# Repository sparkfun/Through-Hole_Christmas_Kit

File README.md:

**NOTE:** *This product has been retired from our catalog.*

Through-Hole Christmas Kit
==========================

[  
*It's A Through-Hole Christmas, Charlie Brown! (KIT-09565)*](https://www.sparkfun.com/products/9565)

This ornamental kit comes with a neatly-cut, tree-shaped PCB, adorned with super-bright green LEDs, and topped with a yellow LED.
The LEDs are controlled by a pre-programmed ATtiny85 AVR, and the circuit is powered by a couple AA batteries. 
All compnents are through-hole, so this is a great kit for that first-time solderer. 

Repository Contents
-------------------
* **/Firmware** - Firmware that ships on the ATtiny85
* **/Hardware** - All Eagle design files (.brd, .sch)

License Information
-------------------
The hardware is released under [Creative Commons Share-alike 3.0](http://creativecommons.org/licenses/by-sa/3.0/).  
All other code is open source so please feel free to do anything you want with it; you buy me a beer if you use this and we meet someday ([Beerware license](http://en.wikipedia.org/wiki/Beerware)).

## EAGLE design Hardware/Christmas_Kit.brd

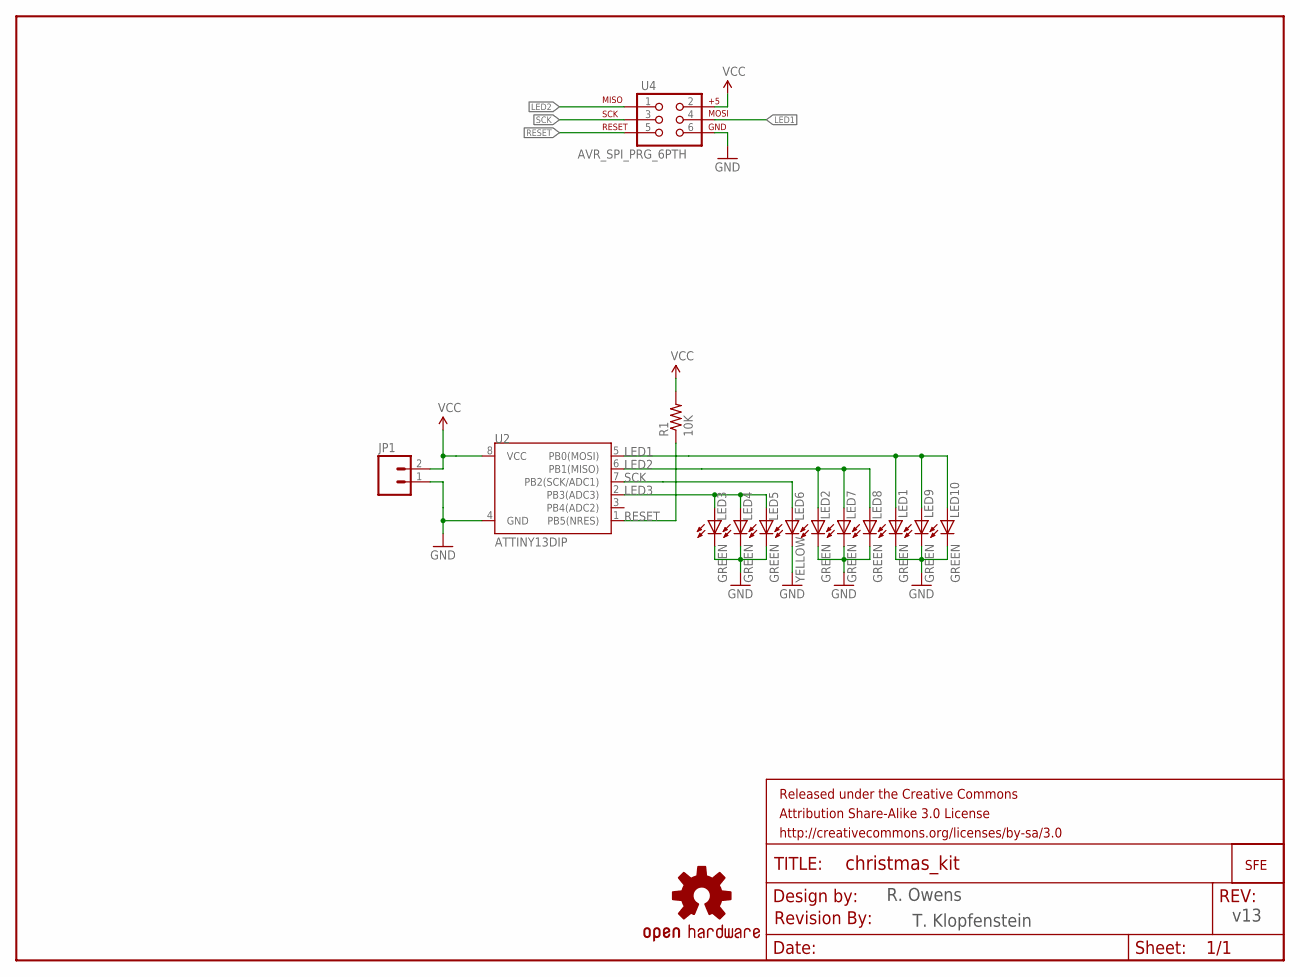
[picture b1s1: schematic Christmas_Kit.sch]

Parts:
FRAME1: FRAME-LETTER; CREATIVE_COMMONS
JP1: M02PTH; 1X02
JP2: LOGO-SFENEW; SFE-NEW-WEBLOGO
LED1, LED2, LED3, LED4, LED5, LED7, LED8, LED9, LED10: GREEN; LED5MM
LED6: YELLOW; LED3MM
LOGO1: OSHW-LOGOL; OSHW-LOGO-L
R1: 10K; AXIAL-0.3
U2: ATTINY13DIP; DIP08
U4: AVR_SPI_PRG_6PTH; 2X3
U$1: REVISION

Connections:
GND: JP1.1, LED1.K (C), LED2.K (C), LED3.K (C), LED4.K (C), LED5.K (C), LED6.K (C), LED7.K (C), LED8.K (C), LED9.K (C), LED10.K (C), U2.4 (GND), U4.6
LED1: LED1.A, LED9.A, LED10.A, U2.5 (PB0(MOSI)), U4.4
LED2: LED2.A, LED7.A, LED8.A, U2.6 (PB1(MISO)), U4.1
LED3: LED3.A, LED4.A, LED5.A, U2.2 (PB3(ADC3))
RESET: R1.P$1 (1), U2.1 (PB5(NRES)), U4.5
SCK: LED6.A, U2.7 (PB2(SCK/ADC1)), U4.3
VCC: JP1.2, R1.P$2 (2), U2.8 (VCC), U4.2

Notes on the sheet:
R. Owens
v13
T. Klopfenstein

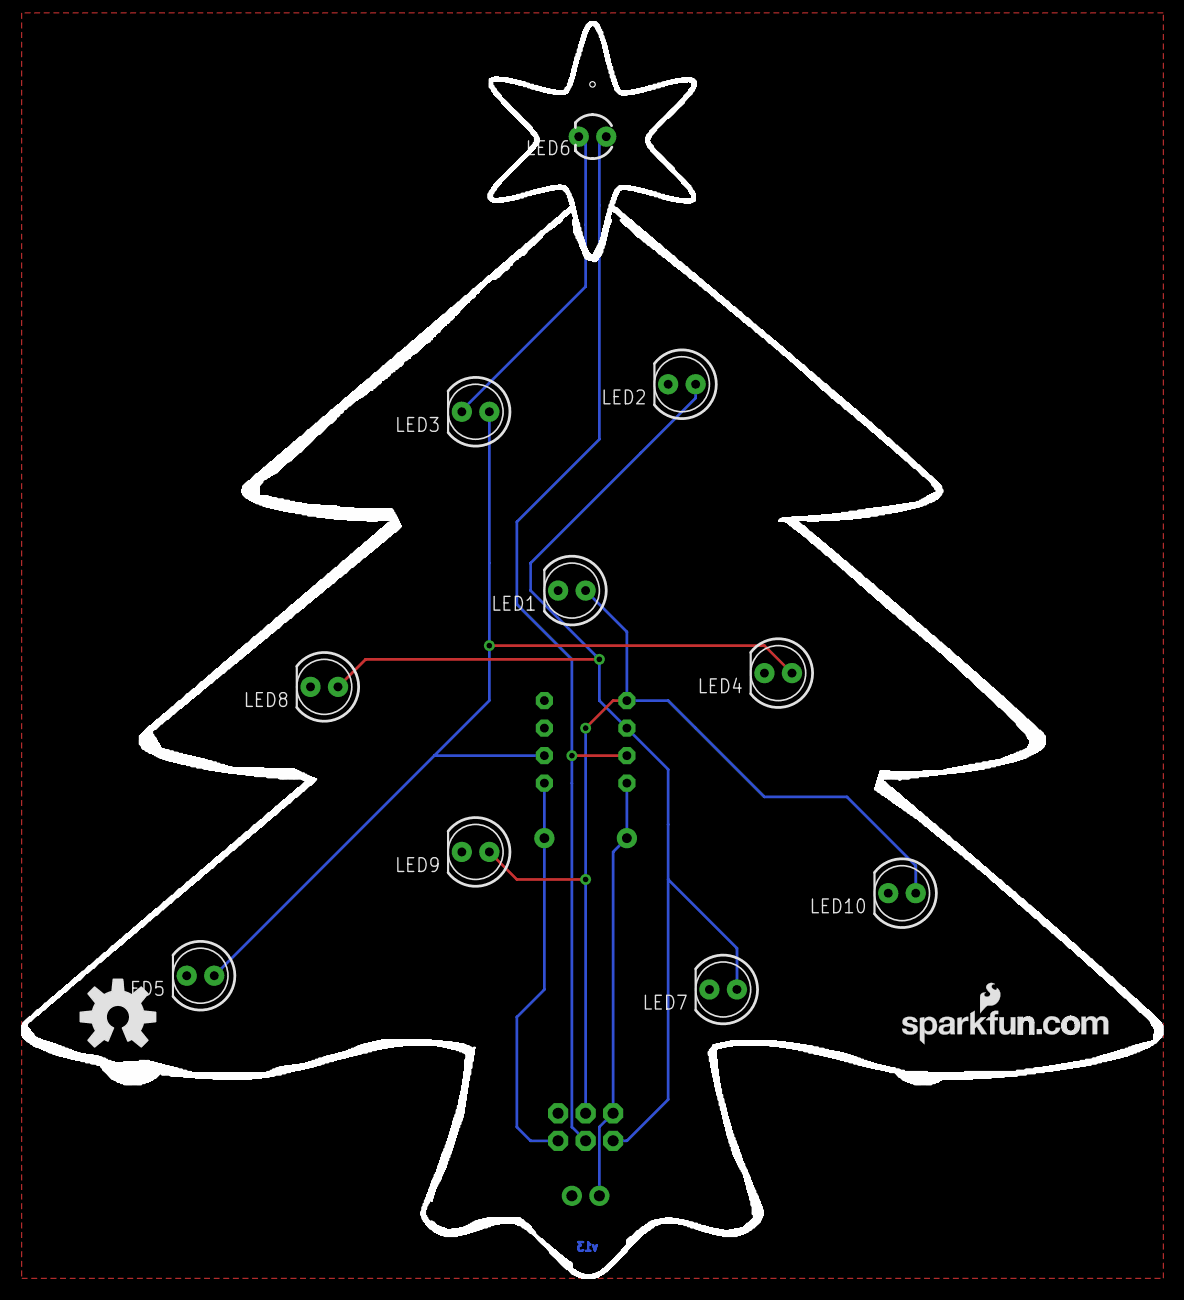
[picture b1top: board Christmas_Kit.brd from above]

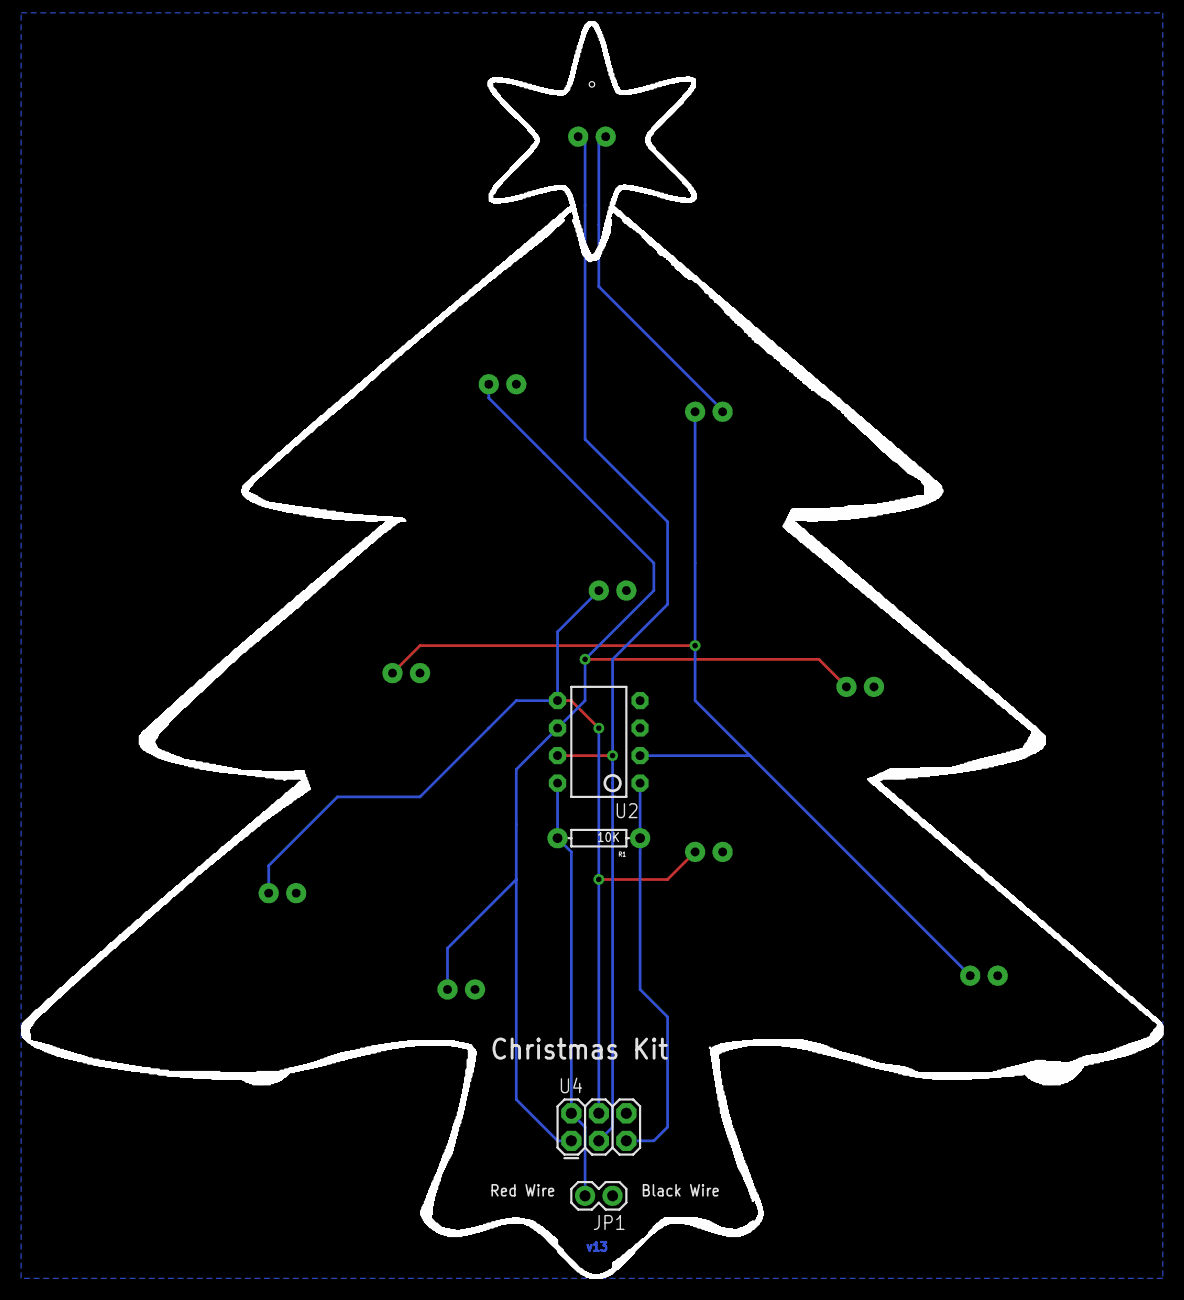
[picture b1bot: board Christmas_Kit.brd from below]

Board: 2 copper layers, 105.4 x 116.0 mm, 18 parts (4 on the bottom side), 7 nets.

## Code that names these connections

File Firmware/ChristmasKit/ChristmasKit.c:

/********************************************************************************
						Christmas Board Code
					  Copyright Sparfun Electronics
					    Written by Ryan Owens
						      12/4/2008
*********************************************************************************
*/

//***************************************
//			Include Libraries
//***************************************
#include <inttypes.h>
#include <avr/io.h>
#include <avr/interrupt.h>
#include <stdlib.h>
#include <stdio.h>
#include <math.h>

//***************************************
//		Macros and Definitions
//***************************************
#define sbi(var, mask)   ((var) |= (uint8_t)(1 << mask))
#define cbi(var, mask)   ((var) &= (uint8_t)~(1 << mask))

//LED Output Pins (PortB)
#define LED1	0
#define LED4	2
#define LED2	1
#define LED3	3

//LED Macros
#define LED1_ON()	sbi(PORTB, LED1)
#define LED1_OFF()	cbi(PORTB, LED1)

#define LED2_ON()	sbi(PORTB, LED2)
#define LED2_OFF()	cbi(PORTB, LED2)

#define LED3_ON()	sbi(PORTB, LED3)
#define LED3_OFF()	cbi(PORTB, LED3)

#define LED4_ON()	sbi(PORTB, LED4)
#define LED4_OFF()	cbi(PORTB, LED4)

//Program Definitions
#define INT_FREQ 4000
#define FRAME_DEPTH 511

//***************************************
//			Global Variables
//***************************************
volatile int led_brightness;
volatile unsigned long int light_up=0;
volatile int frame_count=0;
volatile int LED=1;

//***************************************
//		Function Prototypes
//***************************************
void ioinit (void);      // initializes IO
void delay_ms(uint16_t x);

//***************************************
//			Main Code
//***************************************
ISR(SIG_OUTPUT_COMPARE0A){
	cli();
	
	
	if(frame_count < FRAME_DEPTH)frame_count+=1;
	else frame_count=0;
	
	if(light_up>0){
		light_up-=1;
		if(led_brightness > frame_count){
			switch (LED)
			{
				case 1:
					LED1_ON();
					break;
				case 2:
					LED2_ON();
					break;
				case 3:
					LED3_ON();
					break;
			}
		}
		else{
			LED1_OFF();
			LED2_OFF();
			LED3_OFF();
		}
	}
	else{
		LED1_OFF();
		LED2_OFF();
		LED3_OFF();
	}
	sei();
}

int main (void)
{
	ioinit();
	light_up=0;

	while(1){
		LED4_ON();
		for(int s_led=2; s_led<5; s_led++)
		{
			LED=s_led;
			for(int brightness=0; brightness <= 100; brightness+=5)
			{
				light_up=2500;
				led_brightness=brightness;
				while(light_up>0);
			}
			for(int brightness=100; brightness >= 0; brightness-=5)
			{
				light_up=2500;
				led_brightness=brightness;
				while(light_up>0);
			}		
		}
		LED4_OFF();
		for(int i=0; i<8; i++)delay_ms(30000);
	}
	
return 0;	
}

void ioinit (void) 
{

	//Set up the I/O
    //1 = output, 0 = input
	DDRB = (1<<LED1) | (1<<LED2) | (1<<LED3) | (1<<LED4); //Enable the LED pins as outputs

	TCCR0A=(1<<WGM01);	//Clear timer on Compare
	TCCR0B=(1<<CS01); //Divide Clock(8MHZ) by 8
	OCR0A=30;	//Set Interrupt frequency to Timer(1mHz)/100=10kHz
	TIMSK = (1<<OCIE0A);		//Interrupt when timer0=OCA
	
	sei(); //Enable interrupts	//Enable Interrupts
}

//General short delays
void delay_ms(uint16_t x)
{
  uint8_t y, z;
  for ( ; x > 0 ; x--){
    for ( y = 0 ; y < 10 ; y++){
      for ( z = 0 ; z < 10 ; z++){
        asm volatile ("nop");
      }
    }
  }
}

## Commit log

2013-07-12 Update to v13
2013-07-15 Updated revision to symbol

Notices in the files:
parts and their libraries:
SparkFun-Aesthetics: Licensing: CC v3.0 Share-Alike You are welcome to use this library for commercial purposes.
SparkFun-Aesthetics: Released under the Creative Commons Attribution Share-Alike 3.0 License
SparkFun-Aesthetics: Released under the Creative Commons
